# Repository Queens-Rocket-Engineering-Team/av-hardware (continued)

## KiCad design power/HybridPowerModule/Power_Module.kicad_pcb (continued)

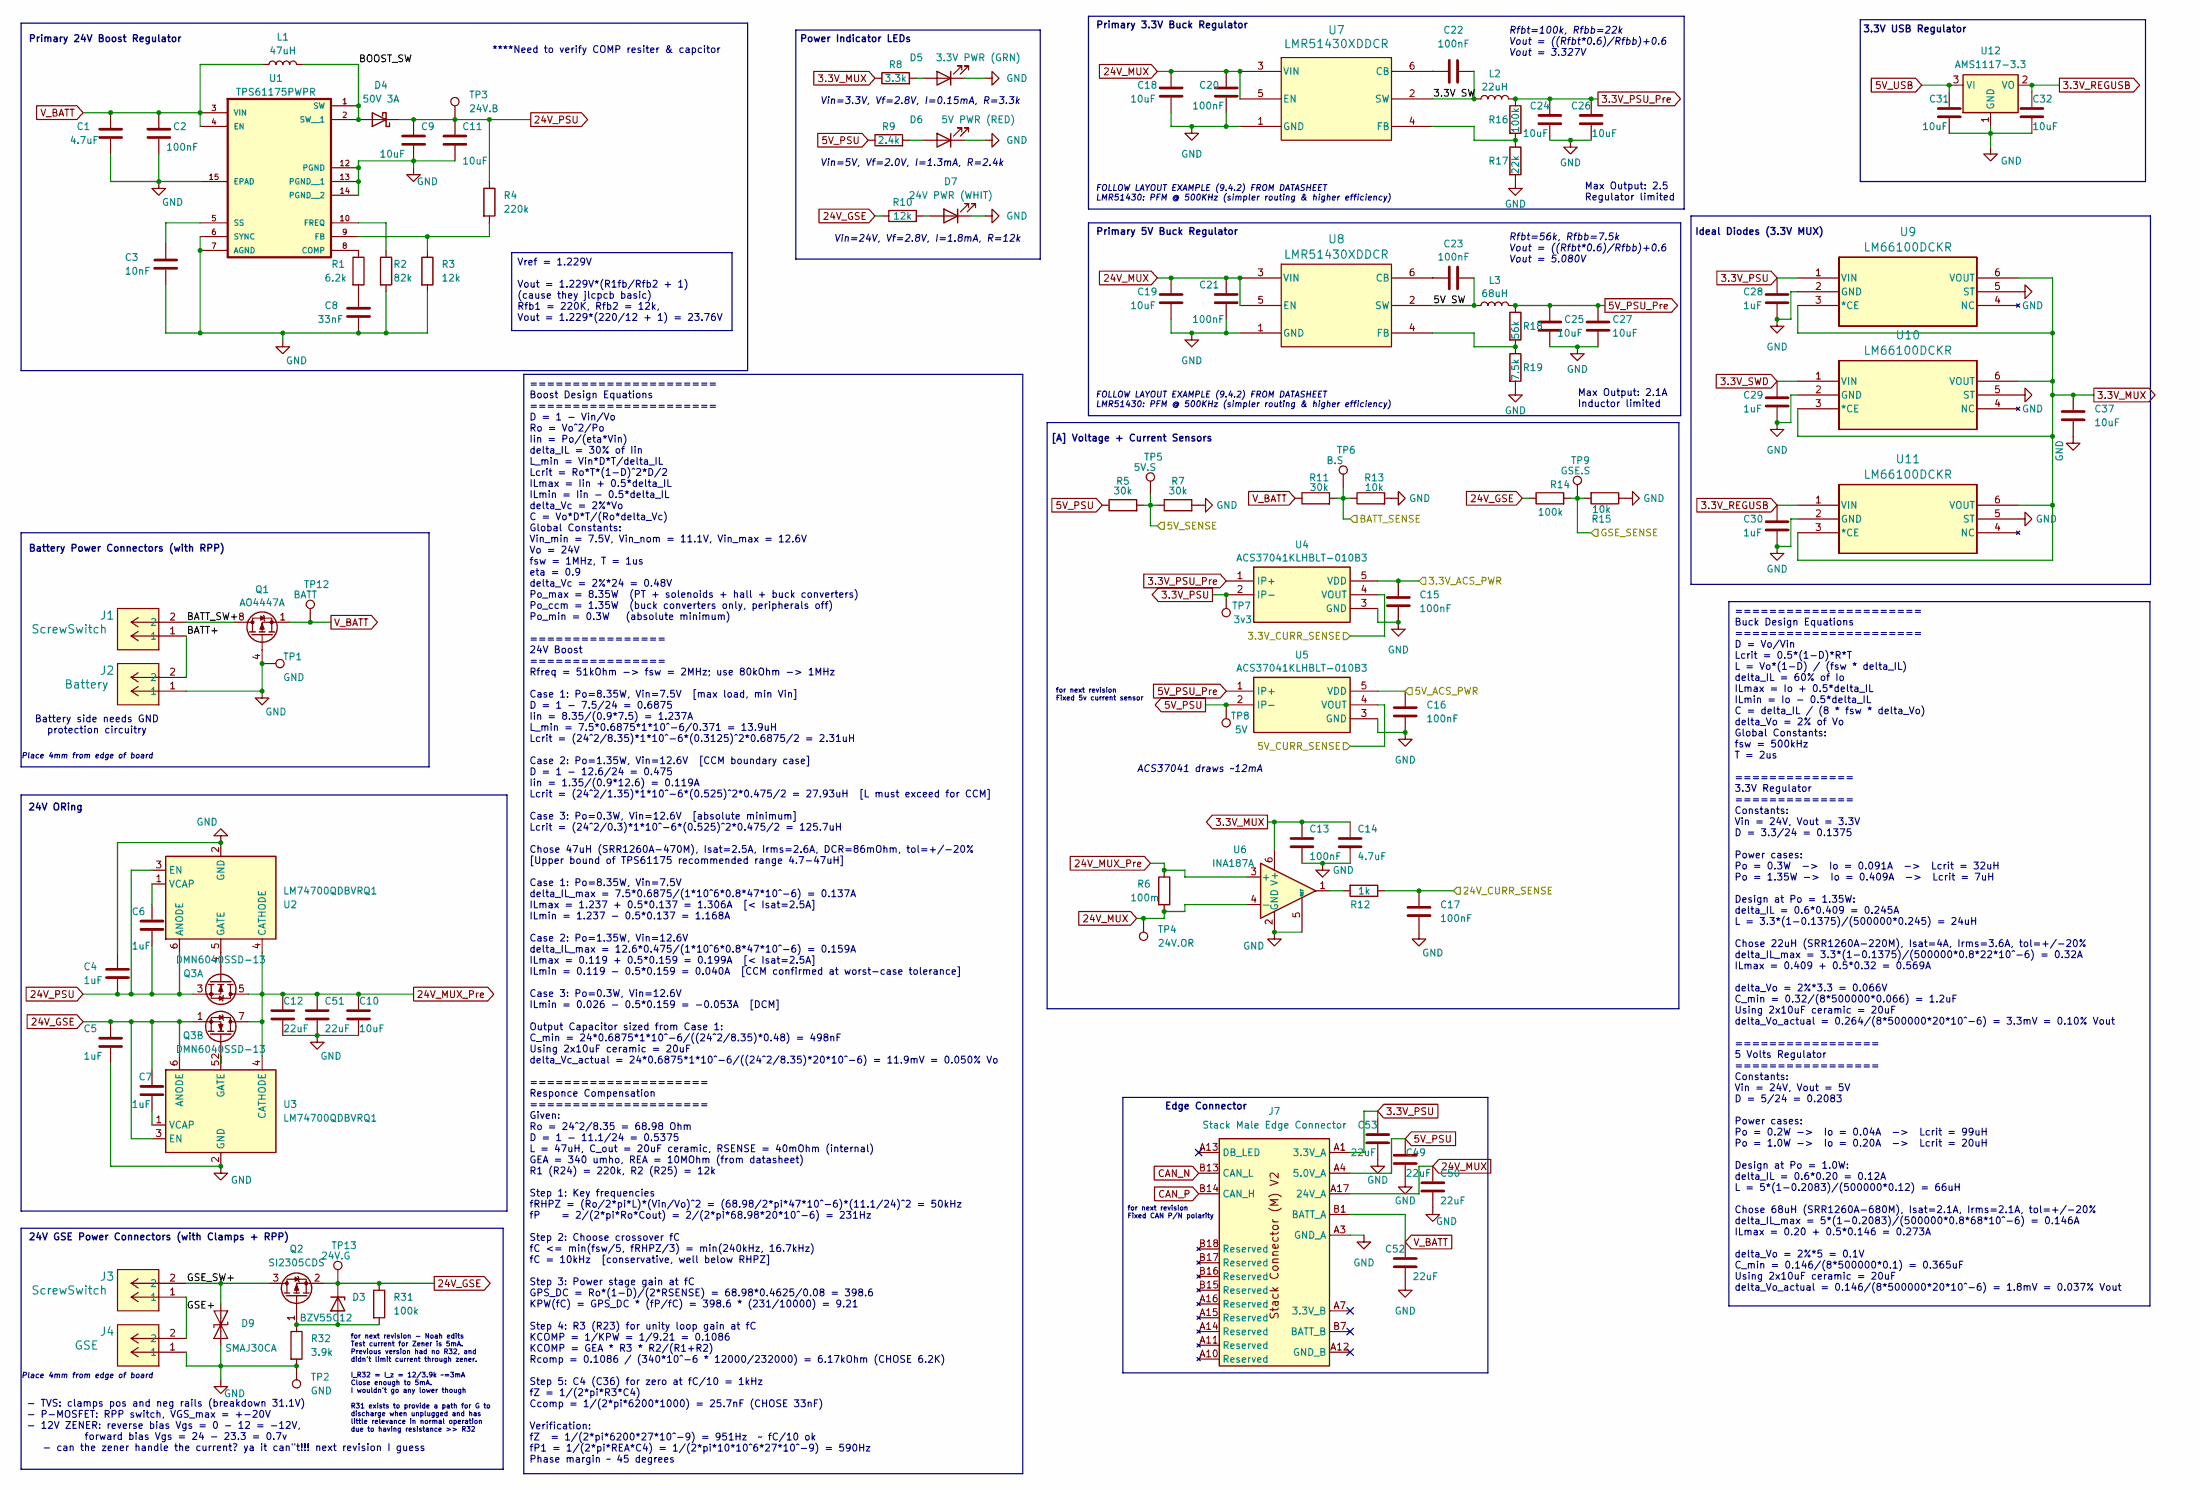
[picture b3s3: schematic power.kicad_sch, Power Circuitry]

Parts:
C1, C14: 4.7uF; C_0805_2012Metric; LCSC C1779
C2, C13, C15, C16, C17, C20, C21, C22, C23: 100nF; C_0603_1608Metric; LCSC C14663
C3: 10nF; C_0603_1608Metric; LCSC C57112
C4, C5, C6, C7, C28, C29, C30: 1uF; C_0603_1608Metric; LCSC C15849
C8: 33nF; C_0603_1608Metric; LCSC C21117
C9, C10, C11, C18, C19: 10uF; C_1206_3216Metric; LCSC C13585
C12, C50, C51: 22uF; C_1206_3216Metric; Digikey 445-8045-1-ND
C24, C25, C26, C27, C37: 10uF; C_0805_2012Metric; LCSC C15850
C31, C32: 10uF; C_0603_1608Metric; LCSC C96446
C49, C52, C53: 22uF; C_1206_3216Metric; LCSC C12891
D3: BZV55C12; D_MiniMELF; LCSC C545360
D4: 50V 3A; D_SMA; Digikey 112-VSSAF5N50-M3/6BCT-ND
D5: 3.3V PWR (GRN); LED_0805_2012Metric; LCSC C2297
D6: 5V PWR (RED); LED_0805_2012Metric; LCSC C84256
D7: 24V PWR (WHIT); LED_0805_2012Metric; LCSC C34499
D9: SMAJ30CA; D_SMA; LCSC C110043
J1, J3: ScrewSwitch; CONN_2-1445057-2_TYCO; Digikey A33212CT-ND
J2: Battery; CONN_2-1445057-2_TYCO; Digikey A33212CT-ND
J4: GSE; CONN_2-1445057-2_TYCO; Digikey A33212CT-ND
J7: Stack Male Edge Connector; BUS_PCIexpress_x1
L1: 47uH; L_Bourns_SRN8040TA; Digikey 283-SDCHA1V8040-470-RCT-ND
L2: 22uH; L_Bourns_SRN8040TA; Digikey 283-SDCHA1V8040-220-RCT-ND
L3: 68uH; L_Bourns_SRN8040TA; Digikey 283-SDCHA1V8040-680-RCT-ND
Q1: AO4447A; SOIC-8_3.9x4.9mm_P1.27mm; LCSC C125867
Q2: SI2305CDS; SOT-23; LCSC C5182095
Q3: DMN6040SSD-13; SOIC-8_3.9x4.9mm_P1.27mm; LCSC C154876
R1: 6.2k; R_0603_1608Metric; LCSC C4260
R2: 82k; R_0603_1608Metric; LCSC C23254
R3, R10: 12k; R_0603_1608Metric; LCSC C22790
R4: 220k; R_0603_1608Metric; LCSC C22961
R5, R7, R11: 30k; R_0603_1608Metric; LCSC C22984
R6: 100m; R_1206_3216Metric_Pad1.30x1.75mm_HandSolder; Digikey P18940CT-ND
R8: 3.3k; R_0603_1608Metric; LCSC C22978
R9: 2.4k; R_0603_1608Metric; LCSC C22940
R12: 1k; R_0603_1608Metric; LCSC C21190
R13, R15: 10k; R_0603_1608Metric; LCSC C25804
R14, R16: 100k; R_0603_1608Metric; LCSC C25803
R17: 22k; R_0603_1608Metric; LCSC C31850
R18: 56k; R_0603_1608Metric; LCSC C23206
R19: 7.5k; R_0603_1608Metric; LCSC C23234
R31: 100k; R_0603_1608Metric; LCSC C23260
R32: 3.9k; R_0603_1608Metric; LCSC C22809
TP1, TP2: GND; TestPoint_Pad_1.5x1.5mm
TP3: 24V.B; TestPoint_Pad_1.5x1.5mm
TP4: 24V.OR; TestPoint_Pad_1.5x1.5mm
TP5: 5V.S; TestPoint_Pad_1.5x1.5mm
TP6: B.S; TestPoint_Pad_1.5x1.5mm
TP7: 3v3; TestPoint_Pad_1.5x1.5mm
TP8: 5V; TestPoint_Pad_1.5x1.5mm
TP9: GSE.S; TestPoint_Pad_1.5x1.5mm
TP12: BATT; TestPoint_Pad_1.5x1.5mm
TP13: 24V.G; TestPoint_Pad_1.5x1.5mm
U1: TPS61175PWPR; IC_TPS27S100BPWPR; Digikey 296-24013-1-ND
U2, U3: LM74700QDBVRQ1; SOT-23-6; LCSC C2941042
U4, U5: ACS37041KLHBLT-010B3; APS12628LLHALTBAP_HandSolder; Digikey 620-ACS37041KLHBLT-010B3CT-ND
U6: INA187A; SOT-23-6; Digikey 296-INA187A1IDBVRCT-ND
U7, U8: LMR51430XDDCR; SOT-23-6_Handsoldering; Digikey 296-LMR51430XDDCRCT-ND
U9, U10, U11: LM66100DCKR; SC-70-6; LCSC C2869734
U12: AMS1117-3.3; SOT-223-3_TabPin2; LCSC C6186

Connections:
3.3V_ACS_PWR: C15.1, U4.5 (VDD); also elsewhere on the board
3.3V_CURR_SENSE: U4.4 (VOUT); also elsewhere on the board
3.3V_MUX: C13.1, C14.1, C37.1, R8.1, U6.6 (V+), U9.3 (*CE), U9.6 (VOUT), U10.3 (*CE), U10.6 (VOUT), U11.3 (*CE), U11.6 (VOUT); also elsewhere on the board
3.3V_PSU: C28.1, C53.1, J7.A1 (3.3V_A), J7.A2 (3.3V_A), TP7.1 (1_1), U4.2 (IP-), U9.1 (VIN)
3.3V_PSU_Pre: C24.1, C26.1, L2.1, R16.1, U4.1 (IP+)
3.3V_REGUSB: C30.1, C32.1, U11.1 (VIN), U12.2 (VO)
3.3V_SWD: C29.1, U10.1 (VIN); also elsewhere on the board
5V_ACS_PWR: C16.1, U5.5 (VDD); also elsewhere on the board
5V_CURR_SENSE: U5.4 (VOUT); also elsewhere on the board
5V_PSU: C49.1, J7.A4 (5.0V_A), J7.A5 (5.0V_A), R5.1, R9.1, TP8.1 (1_1), U5.2 (IP-); also elsewhere on the board
5V_PSU_Pre: C25.1, C27.1, L3.2, R18.1, U5.1 (IP+)
5V_SENSE: R5.2, R7.1, TP5.1 (1_1); also elsewhere on the board
5V_USB: C31.1, U12.3 (VI); also elsewhere on the board
24V_CURR_SENSE: C17.1, R12.1; also elsewhere on the board
24V_GSE: C5.1, C7.1, D3.1 (K), Q2.2 (S), Q3.1 (S1), R10.1, R14.1, R31.1, TP13.1 (1_1), U3.3 (EN), U3.6 (ANODE)
24V_MUX: C18.1, C19.1, C20.1, C21.1, C50.1, J7.A17 (24V_A), J7.A18 (24V_A), R6.2, TP4.1 (1_1), U6.4 (-), U7.3 (VIN), U7.5 (EN), U8.3 (VIN), U8.5 (EN)
24V_MUX_Pre: C10.1, C12.1, C51.1, Q3.5 (D2), Q3.6 (D2), Q3.7 (D1), Q3.8 (D1), R6.1, U2.4 (CATHODE), U3.4 (CATHODE), U6.3 (+)
24V_PSU: C4.2, C6.2, C9.1, C11.1, D4.1 (K), Q3.3 (S2), R4.1, TP3.1 (1_1), U2.3 (EN), U2.6 (ANODE)
/power/3.3V SW: C22.2, L2.2, U7.2 (SW)
/power/5V SW: C23.1, L3.1, U8.2 (SW)
/power/BATT+: J1.1, J2.2
/power/BATT_SW+: J1.2, Q1.5 (D), Q1.6 (D), Q1.7 (D), Q1.8 (D)
/power/BOOST_SW: D4.2 (A), L1.2, U1.1 (SW), U1.2 (SW__1)
/power/GSE+: J3.1, J4.2
/power/GSE_SW+: D9.2 (A2), J3.2, Q2.3 (D)
BATT_SENSE: R11.2, R13.1, TP6.1 (1_1); also elsewhere on the board
CAN_N: J7.B13 (CAN_L); also elsewhere on the board
CAN_P: J7.B14 (CAN_H); also elsewhere on the board
GND: C1.2, C2.2, C3.2, C4.1, C5.2, C8.2, C9.2, C10.2, C11.2, C12.2, C13.2, C14.2, C15.2, C16.2, C17.2, C18.2, C19.2, C20.2, C21.2, C24.2, C25.2, C26.2, C27.2, C28.2, C29.2, C30.2, C31.2, C32.2, C37.2, C49.2, C50.2, C51.2, C52.2, C53.2, D5.1 (K), D6.1 (K), D7.1 (K), D9.1 (A1), J2.1, J4.1, J7.A3 (GND_A), J7.A6 (GND_A), J7.B4 (GND_A), J7.B5 (GND_A), J7.B6 (GND_A), Q1.4 (G), R2.2, R3.2, R7.2, R13.2, R15.1, R17.2, R19.2, R32.2, TP1.1 (1_1), TP2.1 (1_1), U1.6 (SYNC), U1.7 (AGND), U1.12 (PGND), U1.13 (PGND__1), U1.14 (PGND__2), U1.15 (EPAD), U2.2 (GND), U3.2 (GND), U4.3 (GND), U5.3 (GND), U6.2 (GND), U6.5 (REF), U7.1 (GND), U8.1 (GND), U9.2 (GND), U9.5 (ST), U10.2 (GND), U10.5 (ST), U11.2 (GND), U11.5 (ST), U12.1 (GND); also elsewhere on the board
GSE_SENSE: R14.2, R15.2, TP9.1 (1_1); also elsewhere on the board
unnamed: C8.1, R1.2
unnamed: D3.2 (A), Q2.1 (G), R31.2, R32.1
unnamed: D5.2 (A), R8.2
unnamed: D6.2 (A), R9.2
unnamed: D7.2 (A), R10.2
unnamed: Q3.2 (G1), U3.5 (GATE)
unnamed: Q3.4 (G2), U2.5 (GATE)
unnamed: R12.2, U6.1
unnamed: R1.1, U1.8 (COMP)
unnamed: R3.1, R4.2, U1.9 (FB)
unnamed: R2.1, U1.10 (FREQ)
unnamed: C3.1, U1.5 (SS)
unnamed: C6.1, U2.1 (VCAP)
unnamed: C7.2, U3.1 (VCAP)
unnamed: C22.1, U7.6 (CB)
unnamed: R16.2, R17.1, U7.4 (FB)
unnamed: C23.2, U8.6 (CB)
unnamed: R18.2, R19.1, U8.4 (FB)
V_BATT: C1.1, C2.1, C52.1, J7.B1 (BATT_A), J7.B2 (BATT_A), J7.B3 (BATT_A), L1.1, Q1.1 (S), Q1.2 (S), Q1.3 (S), R11.1, TP12.1 (1_1), U1.3 (VIN), U1.4 (EN)

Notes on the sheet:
for next revision Fixed CAN P/N polarity
Vin=3.3V, Vf=2.8V, I=0.15mA, R=3.3k
for next revision Fixed 5v current sensor
Power Indicator LEDs
24V GSE Power Connectors (with Clamps + RPP)
[A] Voltage + Current Sensors
ACS37041 draws ~12mA
FOLLOW LAYOUT EXAMPLE (9.4.2) FROM DATASHEET LMR51430: PFM @ 500KHz (simpler routing & higher efficiency)
Ideal Diodes (3.3V MUX)
Primary 24V Boost Regulator
****Need to verify COMP resiter & capcitor
3.3V USB Regulator
Max Output: 2.5 Regulator limited
for next revision - Noah edits Test current for Zener is 5mA. Previous version had no R32, and didn't limit current through zener. I_R32 = I_z = 12/3.9k ~=3mA Close enough to 5mA. I wouldn't go any lower though R31 exists to provide a path for G to discharge when unplugged and has little relevance 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
Battery Power Connectors (with RPP)
Place 4mm from edge of board
Max Output: 2.1A Inductor limited
Primary 3.3V Buck Regulator
Rfbt=100k, Rfbb=22k Vout = ((Rfbt*0.6)/Rfbb)+0.6 Vout = 3.327V
Rfbt=56k, Rfbb=7.5k Vout = ((Rfbt*0.6)/Rfbb)+0.6 Vout = 5.080V
24V ORing
Vin=5V, Vf=2.0V, I=1.3mA, R=2.4k
Battery side needs GND protection circuitry
- TVS: clamps pos and neg rails (breakdown 31.1V) - P-MOSFET: RPP switch, VGS_max = +-20V - 12V ZENER: reverse bias Vgs = 0 - 12 = -12V, forward bias Vgs = 24 - 23.3 = 0.7v - can the zener handle the current? ya it can"t!!! next revision I guess
Vin=24V, Vf=2.8V, I=1.8mA, R=12k
Edge Connector
Primary 5V Buck Regulator
Vref = 1.229V Vout = 1.229V*(R1fb/Rfb2 + 1) (cause they jlcpcb basic) Rfb1 = 220K, Rfb2 = 12k, Vout = 1.229*(220/12 + 1) = 23.76V
====================== Boost Design Equations ====================== D = 1 - Vin/Vo Ro = Vo^2/Po Iin = Po/(eta*Vin) delta_IL = 30% of Iin L_min = Vin*D*T/delta_IL Lcrit = Ro*T*(1-D)^2*D/2 ILmax = Iin + 0.5*delta_IL ILmin = Iin - 0.5*delta_IL delta_Vc = 2%*Vo C = Vo*D*T/(Ro*delta_Vc) Global Constant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
====================== Buck Design Equations ====================== D = Vo/Vin Lcrit = 0.5*(1-D)*R*T L = Vo*(1-D) / (fsw * delta_IL) delta_IL = 60% of Io ILmax = Io + 0.5*delta_IL ILmin = Io - 0.5*delta_IL C = delta_IL / (8 * fsw * delta_Vo) delta_Vo = 2% of Vo Global Constants: fsw = 500kHz T = 2u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

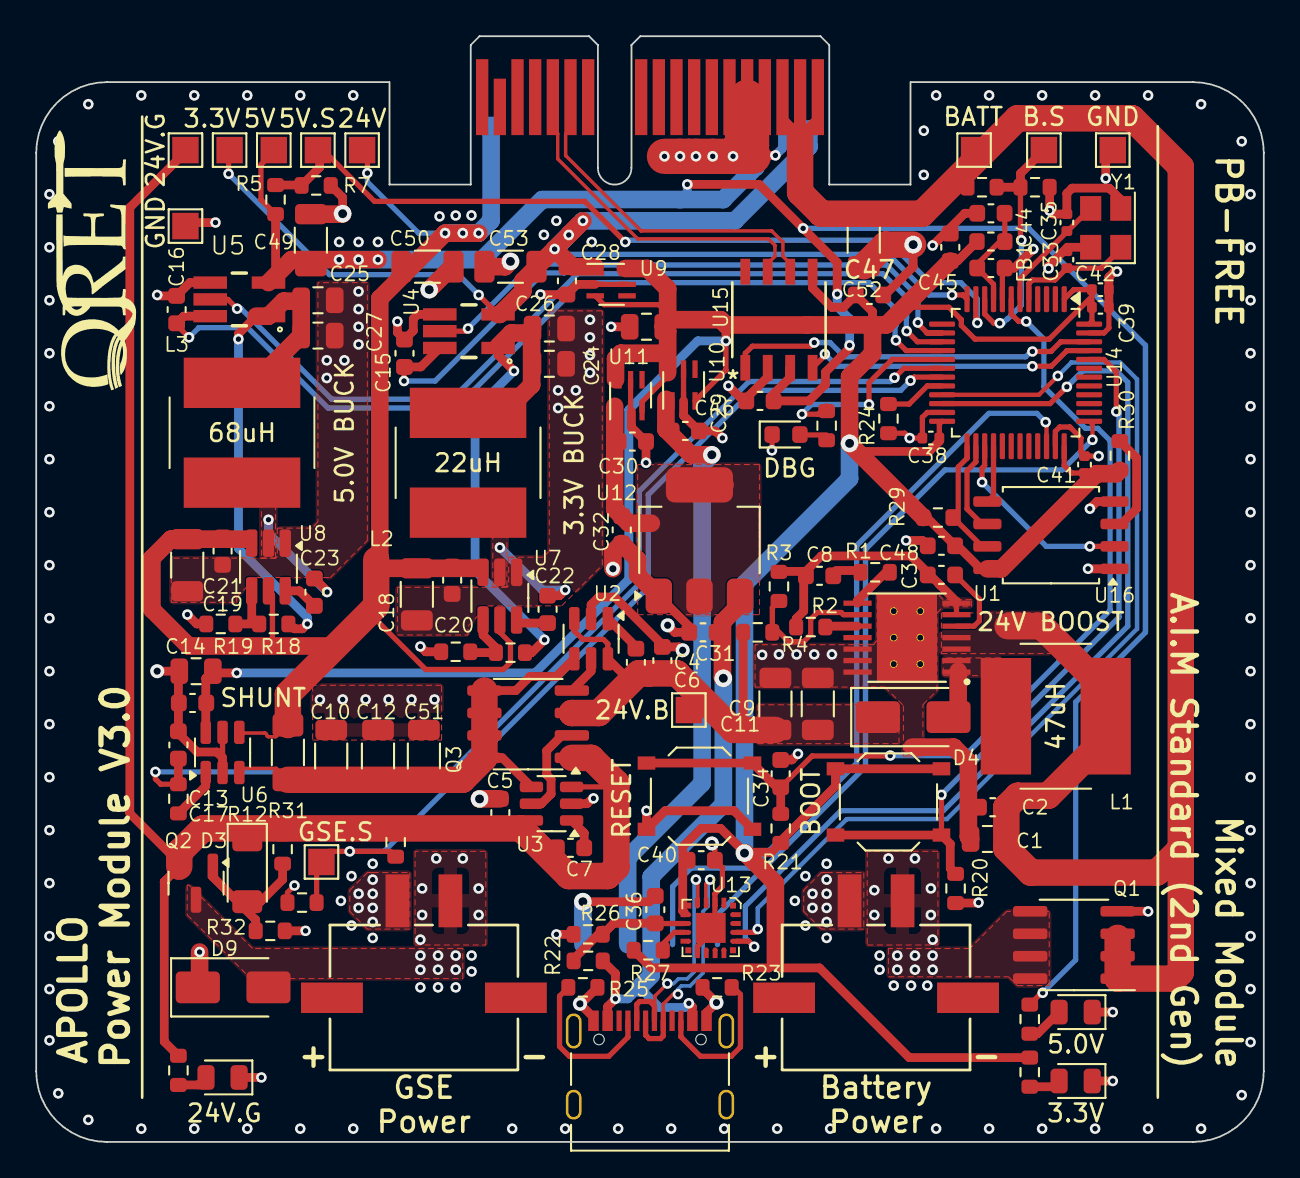
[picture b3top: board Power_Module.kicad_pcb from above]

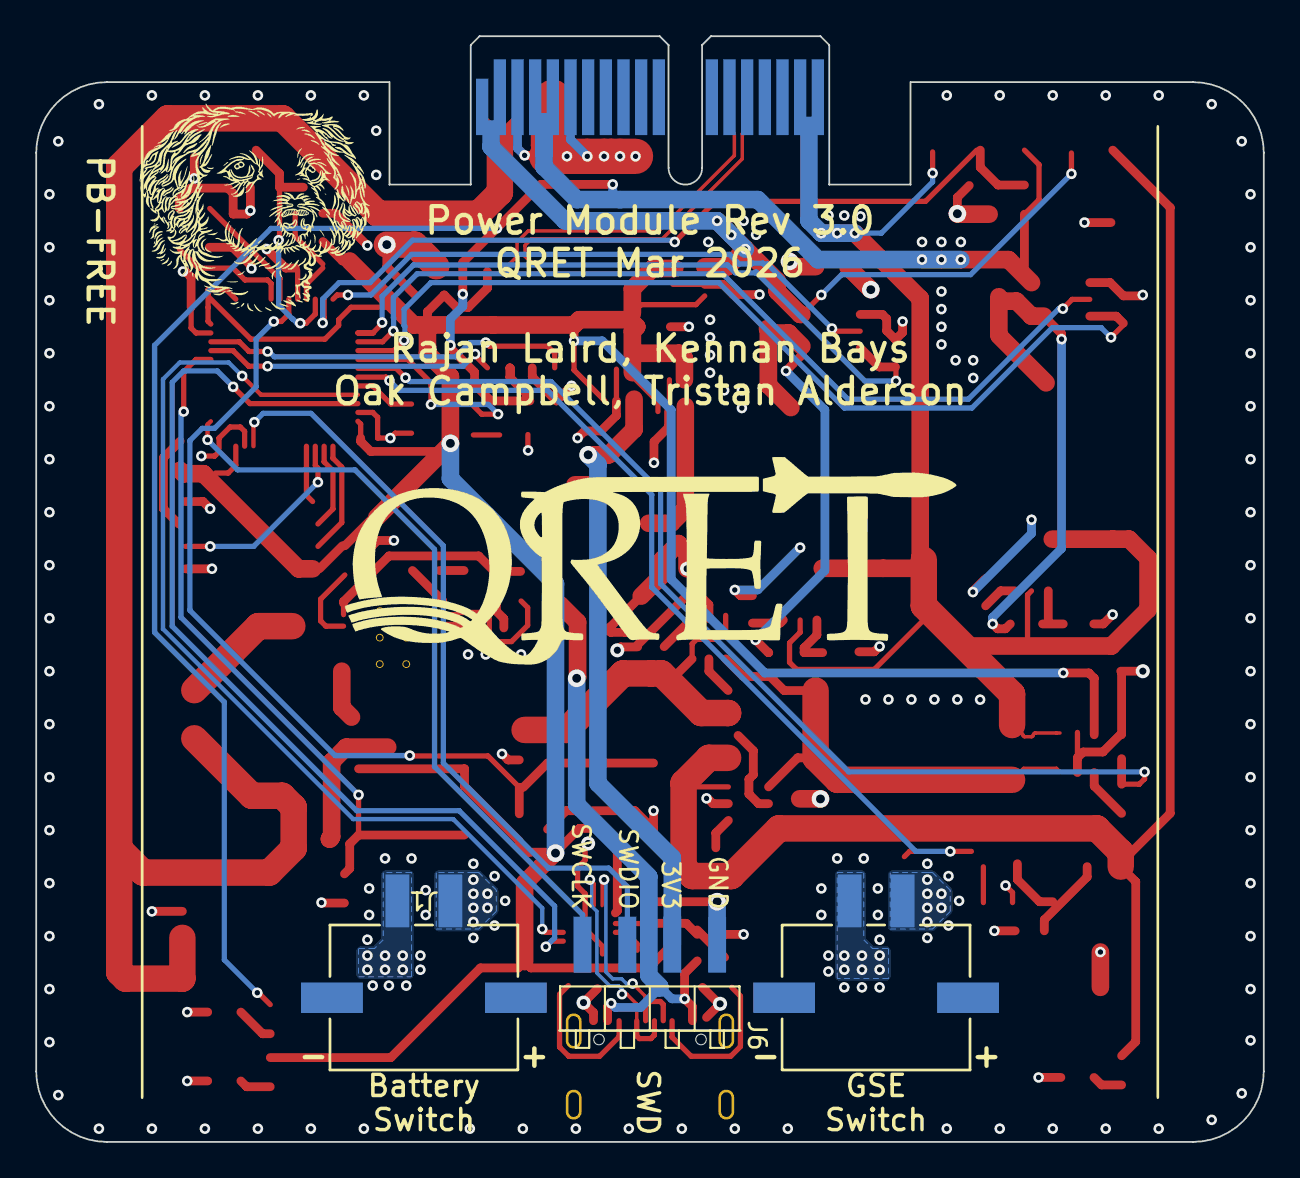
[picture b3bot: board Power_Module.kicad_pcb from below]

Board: 4 copper layers, 69.5 x 62.6 mm, 136 parts (3 on the bottom side), 74 nets.

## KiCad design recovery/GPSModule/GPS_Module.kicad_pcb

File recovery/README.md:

# [System Name]

this is a template and will be filled out soon

[Description of the  system and its purpose]

## Boards

- `[board-name]` - Brief description
- ...

---
QRET, 2026-2027

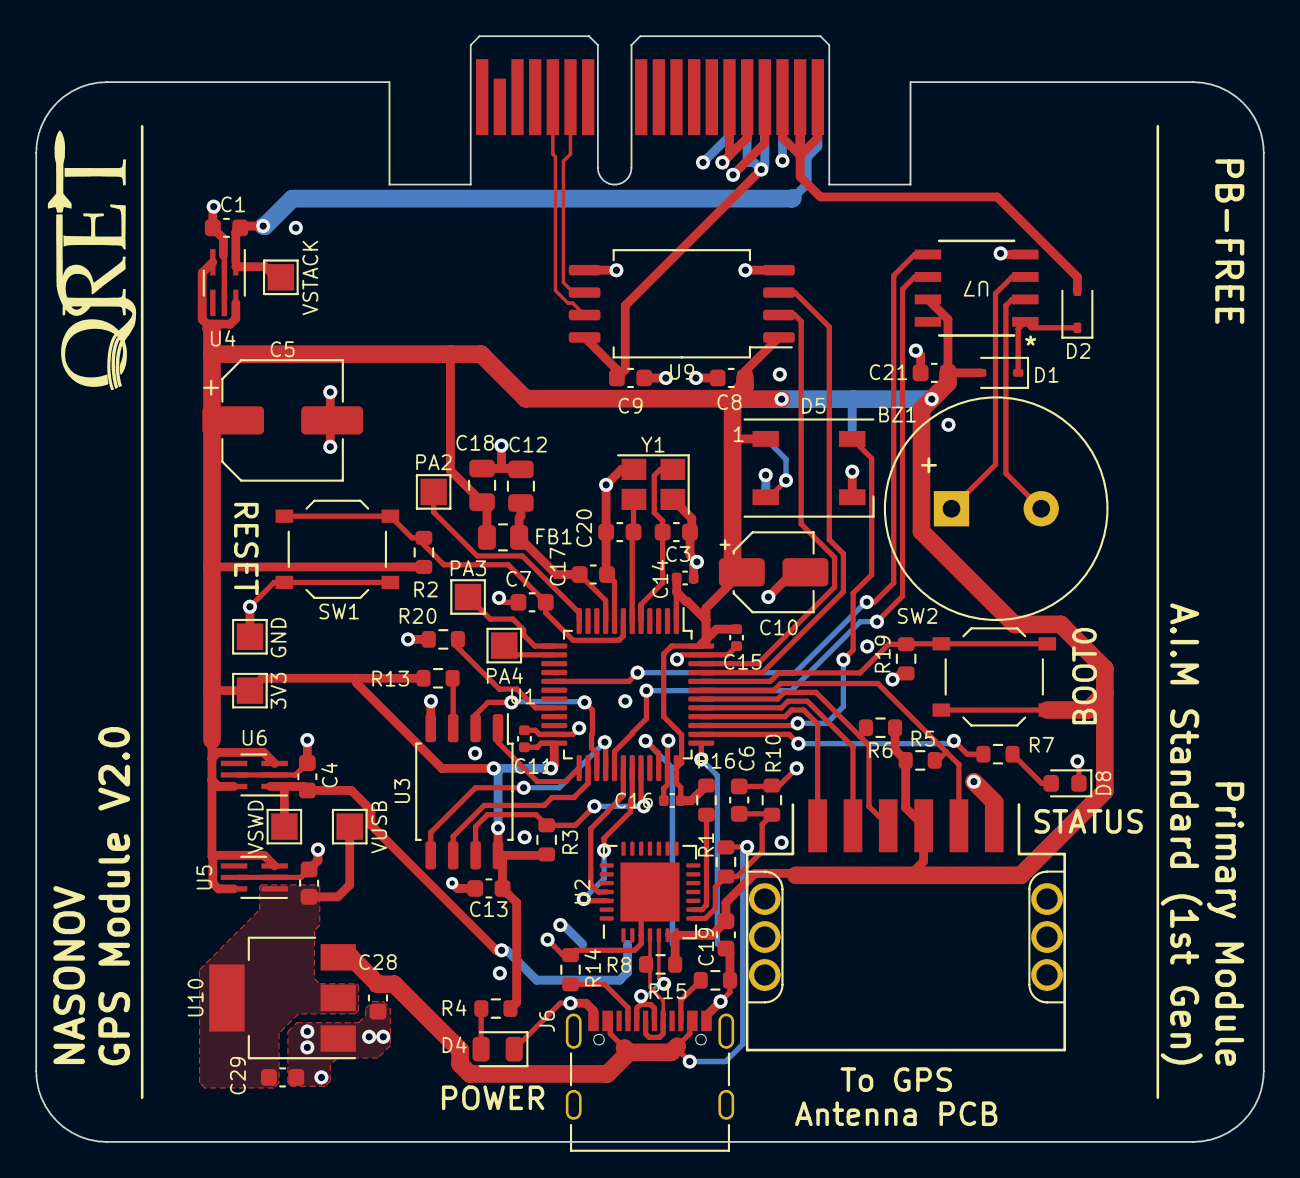
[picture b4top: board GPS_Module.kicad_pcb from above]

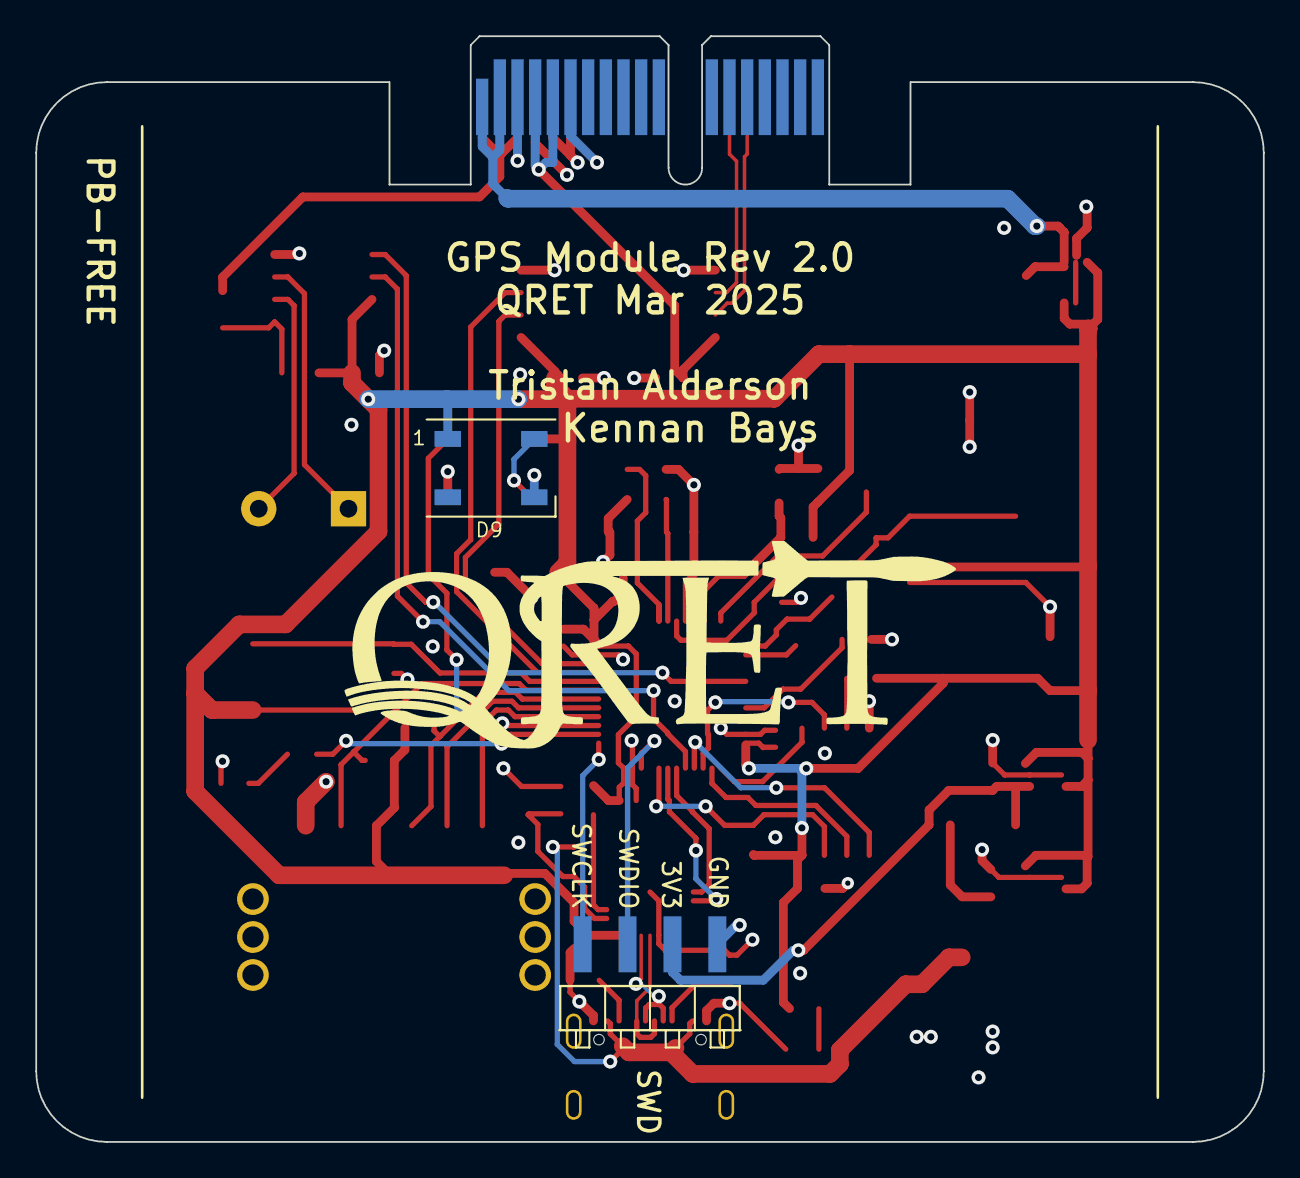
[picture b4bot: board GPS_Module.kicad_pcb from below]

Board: 4 copper layers, 69.5 x 62.6 mm, 70 parts (2 on the bottom side), 51 nets.

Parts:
BZ1: PS1240P02BT; Buzzer_12.6x9.5RM5.0
C1, C2, C4, C6: 1uF; C_0603_1608Metric
C3, C20: 10p; C_0603_1608Metric
C5: 100uF; CP_Elec_6.3x5.9
C7, C13, C21: 100nF; C_0603_1608Metric
C8, C9: 0.1u; C_0603_1608Metric
C10: 10uF; CP_Elec_4x5.4
C11, C14, C15, C16: 100n; C_0402_1005Metric
C12, C18: 1uF; C_0805_2012Metric
C17: 10n; C_0603_1608Metric
C19, C28, C29: 10uF; C_0603_1608Metric
D1, D2: 1N5819WS; D_SOD-323
D4: PWR_LED (GRN); LED_0805_2012Metric
D5, D9: WS2812B; LED_WS2812B_PLCC4_5.0x5.0mm_P3.2mm
D8: DB_LED (YLW); LED_0603_1608Metric
FB1: 100R; R_0805_2012Metric
J1: GT8E-6P-2H(55); CONN_GT8E-6P-2H(55)
J2: SWD_01x04_Pin; SWD_PinHeader_1x04_P2.54mm_Horizontal_SMD
J4: Stack Male Edge Connector; BUS_PCIexpress_x1
J6: USB_C_Female_USB2_Small; USB_C_DB-108PWB
R1: 22k; R_0603_1608Metric
R2, R3, R13: 10k; R_0603_1608Metric
R4: 3.3k; R_0603_1608Metric
R5, R6: 2.2k; R_0603_1608Metric
R7: 680; R_0603_1608Metric
R8: 1.5k; R_0603_1608Metric
R10: 47k; R_0603_1608Metric
R14, R15: 5.1k; R_0603_1608Metric
R16: 1k; R_0603_1608Metric
R19, R20: 100k; R_0603_1608Metric
SW1: SW_STM_RESET; SW_Push_1P1T_XKB_TS-1187A
SW2: SW_STM_BOOT_MODE; SW_Push_1P1T_XKB_TS-1187A
TP1: VSTACK; TestPoint_Pad_1.5x1.5mm
TP2: VUSB; TestPoint_Pad_1.5x1.5mm
TP3: VSWD; TestPoint_Pad_1.5x1.5mm
TP4: PA4; TestPoint_Pad_1.5x1.5mm
TP6: GND; TestPoint_Pad_1.5x1.5mm
TP7: 3V3; TestPoint_Pad_1.5x1.5mm
TP10: PA2; TestPoint_Pad_1.5x1.5mm
TP11: PA3; TestPoint_Pad_1.5x1.5mm
U1: STM32F103CBT6; LQFP-48_7x7mm_P0.5mm
U2: CP2102N-Axx-xQFN28; QFN-28-1EP_5x5mm_P0.5mm_EP3.35x3.35mm
U3: W25Q128JVS; SOIC-8_5.23x5.23mm_P1.27mm
U4, U5, U6: LM66100DCKR; SC-70-6_Handsoldering
U7: TPM8837C-SO1R; SOP-8_TPK
U9: ISO1042BQDWVR; SOIC-8 ISO1042BDWV
U10: AMS1117-3.3; SOT-223-3_TabPin2
Y1: X322516MMB4SI; Crystal_SMD_3225-4Pin_3.2x2.5mm

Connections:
5V_RAW: C28.1, J6.A4 (VBUS), J6.A9 (VBUS), J6.B4 (VBUS), J6.B9 (VBUS), R1.2, U10.3 (VI)
+3.3V: C5.1, C8.2, C10.1, C11.1, C13.1, C14.1, C15.1, C16.1, C18.1, C19.2, C21.1, D1.2 (A), D5.1 (VDD), D9.1 (VDD), FB1.2, J1.3, R2.2, R3.2, R4.2, R5.2, R6.1, R8.1, R13.2, R16.2, SW2.2, TP7.1, U1.1 (VBAT), U1.24 (VDD), U1.36 (VDD), U1.48 (VDD), U2.6 (VDD), U2.7 (VREGIN), U3.8 (VCC), U4.3 (*CE), U4.6 (VOUT), U5.3 (*CE), U5.6 (VOUT), U6.3 (*CE), U6.6 (VOUT), U7.7 (NSLEEP), U7.8 (VCC), U9.1 (VCC1)
+3.3VA: C12.1, C17.1, FB1.1, U1.9 (VDDA)
+5V: C9.2, J4.A4 (5.0V_A), J4.A5 (5.0V_A), U9.8 (VCC2)
+BATT: D2.2 (A), J4.B1 (BATT_A), J4.B2 (BATT_A), J4.B3 (BATT_A)
BOOT0: R19.2, SW2.1, U1.44 (BOOT0)
BOOT1: R20.2, U1.20 (PB2)
BUZZER_A: U1.29 (PA8), U7.6 (IN1)
BUZZER_B: U1.17 (PA7), U7.5 (IN2)
CAN_H: J4.B14 (CAN_H), U9.7 (CANH)
CAN_L: J4.B13 (CAN_L), U9.6 (CANL)
CAN_RX: U1.45 (PB8), U9.3 (RXD)
CAN_TX: U1.46 (PB9), U9.2 (TXD)
CS_FL: U1.25 (PB12), U3.1 (~CS)
DB_LED: R7.2, U1.38 (PA15)
EXTINT_GPS: J1.5, U1.41 (PB5)
GND: C1.2, C2.2, C3.2, C4.2, C5.2, C6.1, C7.2, C8.1, C9.1, C10.2, C11.2, C12.2, C13.2, C14.2, C15.2, C16.2, C17.2, C18.2, C19.1, C20.2, C21.2, C28.2, C29.2, D4.1 (K), D5.3 (VSS), D8.1 (K), D9.3 (VSS), J1.1, J2.1 (GND), J4.A3 (GND_A), J4.A6 (GND_A), J4.B4 (GND_A), J4.B5 (GND_A), J4.B6 (GND_A), J6.A1 (GND), J6.A12 (GND), J6.B1 (GND), J6.B12 (GND), R10.1, R14.2, R15.2, R19.1, R20.1, SW1.1, TP6.1, U1.8 (VSSA), U1.23 (VSS), U1.35 (VSS), U1.47 (VSS), U2.3 (GND), U2.29 (GND), U3.4 (GND), U4.2 (GND), U4.5 (ST), U5.2 (GND), U5.5 (ST), U6.2 (GND), U6.5 (ST), U7.4 (GND), U9.4 (GND1), U9.5 (GND2), U10.1 (GND), Y1.2, Y1.4
MISO_FL: U1.27 (PB14), U3.2 (DO(IO1))
MOSI_FL: U1.28 (PB15), U3.5 (DI(IO0))
unnamed: BZ1.2 (+), U7.2 (OUT1)
unnamed: BZ1.1 (-), U7.3 (OUT2)
unnamed: D1.1 (K), D2.1 (K), U7.1 (VM)
unnamed: D4.2 (A), R4.1
unnamed: D5.2 (DOUT), D9.4 (DIN)
unnamed: D8.2 (A), R7.1
unnamed: J6.A5 (CC1), R14.1
unnamed: J6.B5 (CC2), R15.1
unnamed: TP10.1, U1.12 (PA2)
unnamed: TP11.1, U1.13 (PA3)
unnamed: TP4.1, U1.14 (PA4)
unnamed: C6.2, R1.1, R10.2, U2.8 (VBUS)
unnamed: R16.1, U2.9 (~RST)
unnamed: R13.1, U3.3 (IO2)
OSC_IN: C3.1, U1.5 (PD0), Y1.1
OSC_OUT: C20.1, U1.6 (PD1), Y1.3
RESET_FL: R3.1, U1.32 (PA11), U3.7 (IO3)
RGB_DATA: D5.4 (DIN), U1.39 (PB3)
RST_GPS: J1.6, U1.40 (PB4)
SCK_FL: U1.26 (PB13), U3.6 (CLK)
SCL_GPS: J1.4, R6.2, U1.42 (PB6)
SDA_GPS: J1.2, R5.1, U1.43 (PB7)
STM_RESET: C7.1, R2.1, SW1.2, U1.7 (NRST)
SWCLK: J2.4 (SWCLK), U1.37 (PA14)
SWDIO: J2.3 (SWDIO), U1.34 (PA13)
USB_D+: J6.A6 (D+), J6.B6 (D+), R8.2, U2.4 (D+)
USB_D-: J6.A7 (D-), J6.B7 (D-), U2.5 (D-)
USB_RX: U1.31 (PA10), U2.26 (TXD)
USB_TX: U1.30 (PA9), U2.25 (RXD)
V_PSU: C1.1, J4.A1 (3.3V_A), J4.A2 (3.3V_A), TP1.1, U4.1 (VIN)
V_REGUSB: C2.1, C29.1, TP2.1, U5.1 (VIN), U10.2 (VO)
V_SWD: C4.1, J2.2 (3V3), TP3.1, U6.1 (VIN)
